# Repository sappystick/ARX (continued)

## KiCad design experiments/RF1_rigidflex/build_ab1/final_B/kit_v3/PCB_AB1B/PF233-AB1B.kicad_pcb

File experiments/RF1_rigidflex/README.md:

# RF1: rigid-flex redesign, side experiment (started 2026-10-29)

**Status: MODELED side experiment, phase 1 done.** Not part of the sign-off, the pipeline, the regress suite or any release. The baseline design is read and never written: every input the study reads is recorded with its sha256 in `results/rf1_phase1.json` together with the baseline commit. Any generator that a later phase changes is first copied into `experiments/RF1_rigidflex/src/` and changed there.

**Fixed (owner, 2026-10-29):** receive coils SB1R-QA/QB, the HTA antenna, the six TX formers and their litz, every printed part. **Free:** how the electronics are split into boards and how they connect: flex, rigid-flex or the circular rigid boards.

## Concepts

| | A: catalog FFC (B12 decision) | B: soldered flex jumpers | C: head rigid-flex (RF1 main line) |
|---|---|---|---|
| What | separate rigid boards, 0.5 mm FFC + connectors at the duct edges | separate rigid boards, custom 2-layer flex strips soldered / hot-bar bonded to pads (no connector) | AB1A + AB1B + CB1D + LB1 one rigid-flex panel (6L rigid sections, 2L flex core), HTA a flex tail, SB1R leads a soldered flex jumper |
| Hand joints in the head (today 66) | 18 (LB1, HTA and SB1R wires stay; the link becomes 4 reflowed connectors) | 12 bonded ends | 5 |
| Boards testable alone | yes | yes | no (panel test + test pads) |
| Fab | standard | standard + simple flex | rigid-flex vendor, every change re-spins the panel |

## Phase 1 results (`rf1_study.py`, MODELED / mesh-checked)

| Question | Result |
|---|---|
| AB1 <-> CB1D link fit on the meshes (link_path_check, imported unchanged) | baseline IDC ribbon 6 / 16 FAIL; catalog FFC 0 / 14; rigid-flex hinge (0.2 mm, no connector) 0 / 14 |
| Headroom (rigid-flex hinge) | 10.4 mm under LB1 (ribbon -4.4, FFC 8.4), 7.2 mm under the septum (ribbon -2.6, FFC 5.2) |
| CB1D -> LB1 hinge, CB1D -> HTA tail | rise 10.6 / 15.9 mm, S-fold needs 8.0 mm at a 2.0 mm fold radius (10 x 0.2 mm): both fit; flex about 15 / 21 mm |
| Receive-coil lead pair, 60 mm | loop area 10.2 mm2 (AWG36 touching) to 60 mm2 (loose 1 mm) today, 3.0 mm2 fixed on a broadside flex pair; capacitance about 5 pF either way |
| Eddy rule 5 | the board graph is a tree (no closed loop around the axis); hatched planes in the hinges; FR4 / polyimide stiffeners only (the vendor also offers stainless and aluminium: excluded) |
| Vendor (Rigiflex pages, `ds/`) | D228 fits the 18 x 24 in panel; 0.10 / 0.10 mm trace / space covers our finest; 6L 1.6 mm rigid-flex with 1 oz is a listed build; polyimide er 4, DF 0.04, water absorption 2.9 % |

What this does **not** show yet: any change in leak, noise or detection. The loop-area ratio is geometry only; the pickup needs the TX field along the lead path (phase 2).

## Where the real improvement is

1. **Build quality and repeatability (large, near certain):** 66 -> 5 hand joints in the head; the receive-lead loop area becomes a fixed 3 mm2 instead of 10-60 mm2 that depends on dressing, so the air leak becomes a calibratable constant instead of a per-unit variable. This is the gain RF1 can deliver for sure.
2. **Receive chain clean-sheet (large, MODELED next):** the AB1 sections are laid out from scratch in RF1, so the known receive defects go in at the same time: VREF / VCM buffer stability (OPEN_ITEMS 30), OPA2211 input range (31), chip-orientation robustness (B11), header pad rings (33). These are performance items; the flex is what lets the layout start over without the header constraint.
3. **Digital noise next to the receive coils (medium, to be modeled):** the ADC SPI (SCLK >= 27.2 MHz) runs between hatched ground layers in the hinge instead of an open ribbon.
4. **Not changed by RF1:** TX (litz, 20 A, 460 V taps stay wire, rules 5 / 6), the shaft cords (a 356 mm telescoping stroke needs dynamic flex: not proposed), the neck and handle boards.

## Phases

1. **Done:** census, mesh fit, fold radii, lead loop area, loop check, vendor fit (`results/rf1_phase1.json`, `results/rf1_head_concept.png`).
2. Receive-lead pickup: copy `sbq_sim.py` into `src/`, add the flex-tail path and the TX field along it; leak and its spread (wire dress Monte Carlo vs fixed flex). Hinge crosstalk SCLK -> RX input.
3. Clean-sheet AB1 section: copy `afe_design.py` / `afe_layout.py` into `src/`, apply items 30 / 31 (isolation resistor or reference driver; VCM / amplifier choice) and the rotating decoupling group (B11); route with the repo router.
4. Rigid-flex board definition: one outline with rigid and flex regions, stackup drawing (6L rigid, 2L flex core, coverlay, FR4 stiffeners), hinge routing with hatched GND, fold-line keep-outs (no vias or pads within 1 mm of a fold); DRC with drc.py per region; KiCad 9 has no per-region stackup, so the fab drawing carries it.
5. Compare A / B / C on the same table (fit, leak, noise, joints, test, cost from real quotes) and decide; only then does anything move into the main design (B12).

## Phase 2 results (`rf1_phase2.py`, on a copy of the receive simulation; MODELED)

Receive-lead pickup, 300 units per case, peak mV at turn-off (the same scale as the board leak in `kit_v22/sbq_sim.json`; lead path ASSUMED):

| QA board | mean | sigma | 95 % of units below |
|---|---|---|---|
| AWG36 untwisted (dress varies) | -1.6 | 26.8 | 49.3 |
| AWG36 twisted (5-15 mm pitch) | -0.03 | 0.69 | 1.27 |
| flex broadside pair at the design orientation | 0.09 | 0.15 | 0.31 |
| flex at the worst orientation (routed carelessly) | 3.0 | - | - |
| board leak for comparison: aligned / 0.1 mm / 0.5 mm offset | 0.008 / 0.015 / 0.13 | | |

The lead pair is part of the receive null: untwisted wire alone is 100-1000 x the aligned board leak. Flex cuts the unit-to-unit spread 4-5 x against a good twisted pair, and its mean is a fixed offset (calibratable). The flex must be routed at the design orientation (loop plane along the field): rule for phase 4. QB: 15.6 / 0.63 / 0.08 mV sigma.

Clock crosstalk into the analog lines of the AB1 <-> CB1D link (2D finite-difference C and L, upper bounds on a 100 pF node, 3.3 V edge in 2 ns):

| victim | ribbon (today) | RF1 hinge (guard traces + ground layer) |
|---|---|---|
| MONO_IN, worst aggressor | 437 mV | 7.1 mV |
| MONO_IN from SCLK | 62 mV | 0.22 mV |
| VCM_OUT, worst aggressor | 215 mV | 1.4 mV |

## Cavity and potting (`rf1_cavity.py`, MODELED, envelope volumes)

With hinges instead of headers and three part swaps on CB1D (OKI-78SR module -> TI LMR36015 + Bourns SRN4018-6R8M; Pico 2 W on pins -> chip-down RP2354A without the radio; headers -> hinges), the tallest CB1D part is 2.5 mm (was 10.2) and the tallest AB1 part 1.6 mm (was the 4 mm header + 5 mm socket).

| layer | baseline | needs | saving |
|---|---|---|---|
| L1 gallery | 5.8 | 2.2 | 3.6 |
| L2 analog cell | 10.2 | 6.05 | 4.15 |
| L5 controller | 11.8 | 5.1 | 6.7 |

- **K-top (recommended):** L0-L4 keep their z (nothing near the receive coils moves); L5 shrinks 6.7 mm: head 47.1 -> 40.4 mm. L5 becomes a potted zone (syntactic silicone, 22.8 cm3, 13.7-18.3 g) instead of coat-only: the tube saves 13.7 g, so the head mass is about unchanged (0 to +4.6 g); the gain is protection (moisture, microphonics, better heat path than still air). To re-run: head_crosscheck, the HTA coupling (it moves 6.7 mm toward the formers), head thermal with the pour.
- **S (full shrink):** 14.5 mm (head 32.6 mm), but AB1, the septum and the carbonyl-iron absorber move 3.6-7.8 mm toward the receive coils: changes the receive null; not before sbq_sim / check_v22 / head_crosscheck say so.
- Potting: L1 gallery and L2 gel (fixed flex, no connector voids), L4 CI unchanged, L5 SYN (new), every hinge bend outside the pours, LB1 / HTA coat only.

## Phase 4: the head rigid-flex definition (`rf1_phase4.py`, MODELED)

- **Stackup:** 6-layer rigid sections (F, In1 hatched GND, In2, In3, In4 plane / +3V3D island, B) with the 2-layer flex core as In2 / In3: hinge signals leave on In2 over a hatched In3 ground. Rigid 1.602 mm, flex 0.186 mm (vendor: 1.6 / 0.2). LB1 goes 4 -> 6 layers; HTA stays a separate 4-layer board with a hot-bar flex tail (the roof stays removable).
- **Flattened panel:** CB1D at the centre, LB1 across its 15.2 mm S-fold, AB1A / AB1B at the ends of L-shaped 7 mm hinges that leave the CB1D duct edge either side of the LB1 hinge: 332 x 171 mm, fits the 457 x 610 mm panel; copper is 24.5 % of the box (expect a high panel price: get quotes).
- **Fold and transition rules F1-F8:** no via / pad within 1.0 mm of a transition; traces cross folds at 90 deg, no corners or width changes in a bend zone; cross-hatched flex ground; fold radius >= 2.0 mm, static only; FR4 / polyimide stiffeners only (rule 5); no 460 V net on any flex (rule 6); no rigid pour across a fold; ground guards on both sides of every analog hinge line. ASSUMED until the vendor and IPC-2223 confirm.
- **CB1D section:** Pico 2 W module and OKI-78SR leave; RP2354A (QFN-60) + 12 MHz crystal + core inductor + TLV755P 3.3 V and LMR36015 + SRN4018-6R8M come in, placed in the freed areas with 0.3 mm to every kept part (`results/rf1_cb1d_section.png`). The radio leaves with the Pico W (OPEN_ITEMS 42 settled by removal). CB1D is not re-routed in RF1 yet.

## Phase 3: clean-sheet AB1 (`src/ab1/`, MODELED)

`make_rf1_ab1.py` builds the RF1 generator as checked patches of the baseline `afe_design.py` / `afe_layout.py` / `afe_ripup.py`. Changes: hinge-exit lands (J2) and flex-jumper lands (J1) instead of headers; OPA2211 reference VBIAS = 2.5 V (REFOUT through OPA2365 half A, 10 ohm isolation, 1 uF); 1:2 divider into each ADC input (AIN+ 1.25 V DC = VCM); RF 820 ohm (total gain 41.5); 10 ohm isolation on the VCM buffer (OPEN_ITEMS 30); local TLV755P +3V3D next to the ADC island (the hinge no longer carries +3V3D; pin 3 is a ground).

Front-end check (`rf1_frontend_check.py`, against TI SBOS377L and the AD7389-4 Rev. 0): baseline **FAIL** (OPA2211 input 1.25 V, range 2.0-3.6 V); RF1 **PASS** (input 2.5 V, ADC common mode 1.25 V inside 0.2-2.3, offset 0 by construction, 38 % of the ADC differential range used vs 42 % baseline, divider noise 0.1 nV/rtHz vs 1.1 for the amplifier, closed-loop bandwidth 0.96 MHz vs the 318 kHz filter).

Routing (the repo's AB1 router, unchanged rules: track 0.15, clearance 0.16, via 0.508 / 0.254):

- **Routing status: AB1B routed: 0 open; KiCad 9 DRC 0 errors / 0 unconnected (20 dangling-track warnings, the baseline has 19); independent DRC 0 fails, minimum clearance 0.204 mm** (`build_ab1/final_B/`, `results/rf1_ab1_route.json`).
- AB1A: best 2 open (the reference buffer's input and its isolation resistor), see the repair-loop record in `results/rf1_ab1_route.json` when it closes.
- How: the hinge exit (J2 lands) sits where the baseline header was (east edge, next to the ADC) and the hinge folds up there; the north exit toward the duct left 3-15 nets open. Placement of the RF1 parts (and, on AB1B, D2 / RF1 / CF1 nudged in a 2 mm window) is automatic: `src/ab1/autoplace_rf1.py` (pads and bodies checked, 0.5 mm corridor margin, caps anchored to their pins) and `src/ab1/repair_loop.py` (re-places only the parts within 2.5-5.5 mm of a stuck pin, keeps a result only if fewer nets are open).
- Tried and dropped (recorded in the generator as options, off): matched AIN- dividers (more parts, 8-15 open), swapped buffer halves (the LDO then blocks the +3V3D island), no local LDO on AB1A (5-8 open), the north hinge exit (3-15 open).

## Baseline defect found here (recorded in docs/CORRECTIONS.md, 2026-10-29)

The committed AD7389-4 AB1 biases the OPA2211 inputs at VCM = 1.25 V, below their 2.0 V minimum on a single 5 V supply (TI SBOS377L). RF1 fixes it (phase 3).

## Files

- `rf1_study.py` phase 1 study; `rf1_figure.py` the figure; `rf1_phase2.py` lead pickup and crosstalk; `rf1_cavity.py` condensation and potting;
  `src/ab1/make_rf1_ab1.py` the clean-sheet AB1 as checked patches of the baseline generator (writes the RF1 copies `afe_design.py`, `afe_layout.py`, `afe_ripup.py`);
  `rf1_phase4.py` stackup, flattened panel, fold rules, CB1D section; `results/` outputs; `ds/` the Rigiflex pages (owner-supplied, 2026-10-29); `src/sbq_sim_baseline_copy.py` the receive simulation copy.

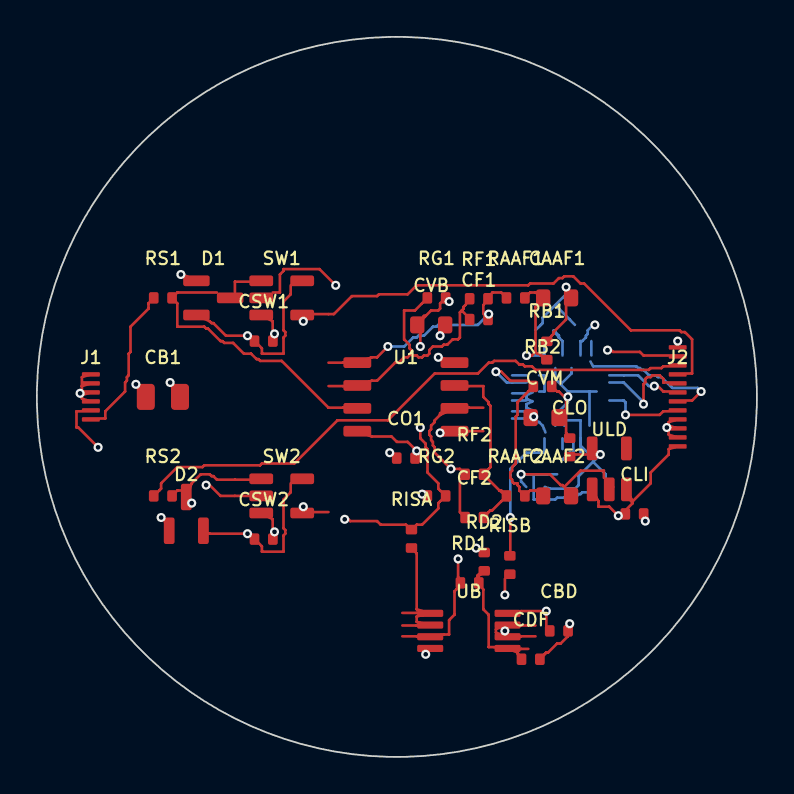
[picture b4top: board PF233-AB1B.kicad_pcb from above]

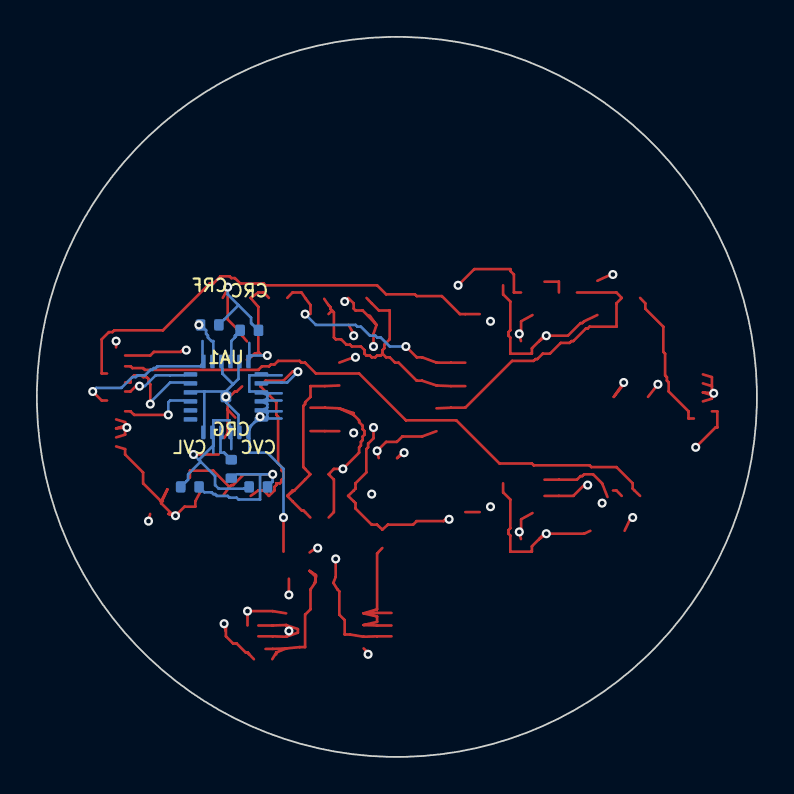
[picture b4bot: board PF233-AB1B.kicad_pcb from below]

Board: 6 copper layers, 40.0 x 40.0 mm, 43 parts (6 on the bottom side), 26 nets.

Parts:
CAAF1, CAAF2: 1n; C_0603_1608Metric
CB1: 10u; C_0805_2012Metric
CBD: 100n; C_0402_1005Metric
CDF: 100n; C_0402_1005Metric
CF1, CF2: 22p; C_0402_1005Metric
CLI: 1u; C_0402_1005Metric
CLO: 1u; C_0402_1005Metric
CO1: 100n; C_0402_1005Metric
CRC: 100n; C_0402_1005Metric
CRF: 1u; C_0402_1005Metric
CRG: 1u; C_0402_1005Metric
CSW1, CSW2: 100n; C_0402_1005Metric
CVB: 1u; C_0603_1608Metric
CVC: 1u; C_0402_1005Metric
CVL: 1u; C_0402_1005Metric
CVM: 1u; C_0603_1608Metric
D1, D2: BAV199; SOT-23
J1: RF1 receive-coil flex jumper lands 6p; FPC_6_P0.5
J2: RF1 rigid-flex hinge exit 12p; FPC_12_P0.5
RAAF1, RAAF2: 1k; R_0402_1005Metric
RB1, RB2: 1k; R_0402_1005Metric
RD1, RD2: 100k; R_0402_1005Metric
RF1, RF2: 820; R_0402_1005Metric
RG1, RG2: 10; R_0402_1005Metric
RISA: 10; R_0402_1005Metric
RISB: 10; R_0402_1005Metric
RS1, RS2: 1000; R_0402_1005Metric
SW1, SW2: 74LVC1G66; SOT-23-5
U1: OPA2211; SOIC-8_3.9x4.9mm_P1.27mm
UA1: AD7389-4; CP-24-25_ADI_LFCSP-24-1EP_4x4mm_P0.5mm_EP0.61x0.61mm
UB: OPA2365; MSOP-8_3x3mm_P0.65mm
ULD: TLV755P33; SOT-23-5

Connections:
+3V3D: CLO.1, CVC.1, CVL.1, UA1.2, UA1.4, ULD.5
+5VA: CB1.1, CBD.1, CLI.1, CO1.1, CSW1.1, CSW2.1, D1.2, D2.2, J2.1, SW1.5, SW2.5, U1.8, UB.8, ULD.1, ULD.3
ADCIN_MONO: CAAF2.1, RAAF2.2, RB2.1, UA1.11
ADCIN_Y8: CAAF1.1, RAAF1.2, RB1.1, UA1.13
BLANK: J2.9, SW1.4, SW2.4
CS: J2.6, UA1.18
FB_MONO: CF2.1, RF2.1, RG2.1, U1.6
FB_Y8: CF1.1, RF1.1, RG1.1, U1.2
GND: CAAF1.2, CAAF2.2, CB1.2, CBD.2, CDF.2, CLI.2, CLO.2, CO1.2, CRC.2, CRF.2, CRG.2, CSW1.2, CSW2.2, CVB.2, CVC.2, CVL.2, CVM.2, D1.1, D2.1, J1.3, J1.4, J1.5, J1.6, J2.2, J2.3, J2.4, J2.12, RB1.2, RB2.2, RD2.2, SW1.3, SW2.3, U1.4, UA1.1, UA1.5, UA1.14, UA1.16, UA1.21, UA1.25, UB.4, ULD.2
IN_MONO: D2.3, RS2.2, SW2.1, U1.5
IN_Y8: D1.3, RS1.2, SW1.1, U1.3
OUT_MONO: CF2.2, RAAF2.1, RF2.2, U1.7
OUT_Y8: CF1.2, RAAF1.1, RF1.2, U1.1
RAW_MONO: J2.10, RS2.1
RAW_Y8: J1.1, RS1.1
REFCAP: CRC.1, UA1.15
REGCAP: CRG.1, UA1.3
SCLK: J2.5, UA1.22
SDO1: J2.7, UA1.19
SDO2: J2.8, UA1.20
VBIAS: CVB.1, J1.2, J2.11, RG1.2, RG2.2, RISA.2, SW1.2, SW2.2
VBIAS_O: RISA.1, UB.1, UB.2
VCM: CVM.1, RISB.2, UA1.6, UA1.7, UA1.8, UA1.9, UA1.10, UA1.12
VCM_DIV: CDF.1, RD1.2, RD2.1, UB.5
VCM_O: RISB.1, UB.6, UB.7
VREF_RAW: CRF.1, RD1.1, UA1.17, UB.3

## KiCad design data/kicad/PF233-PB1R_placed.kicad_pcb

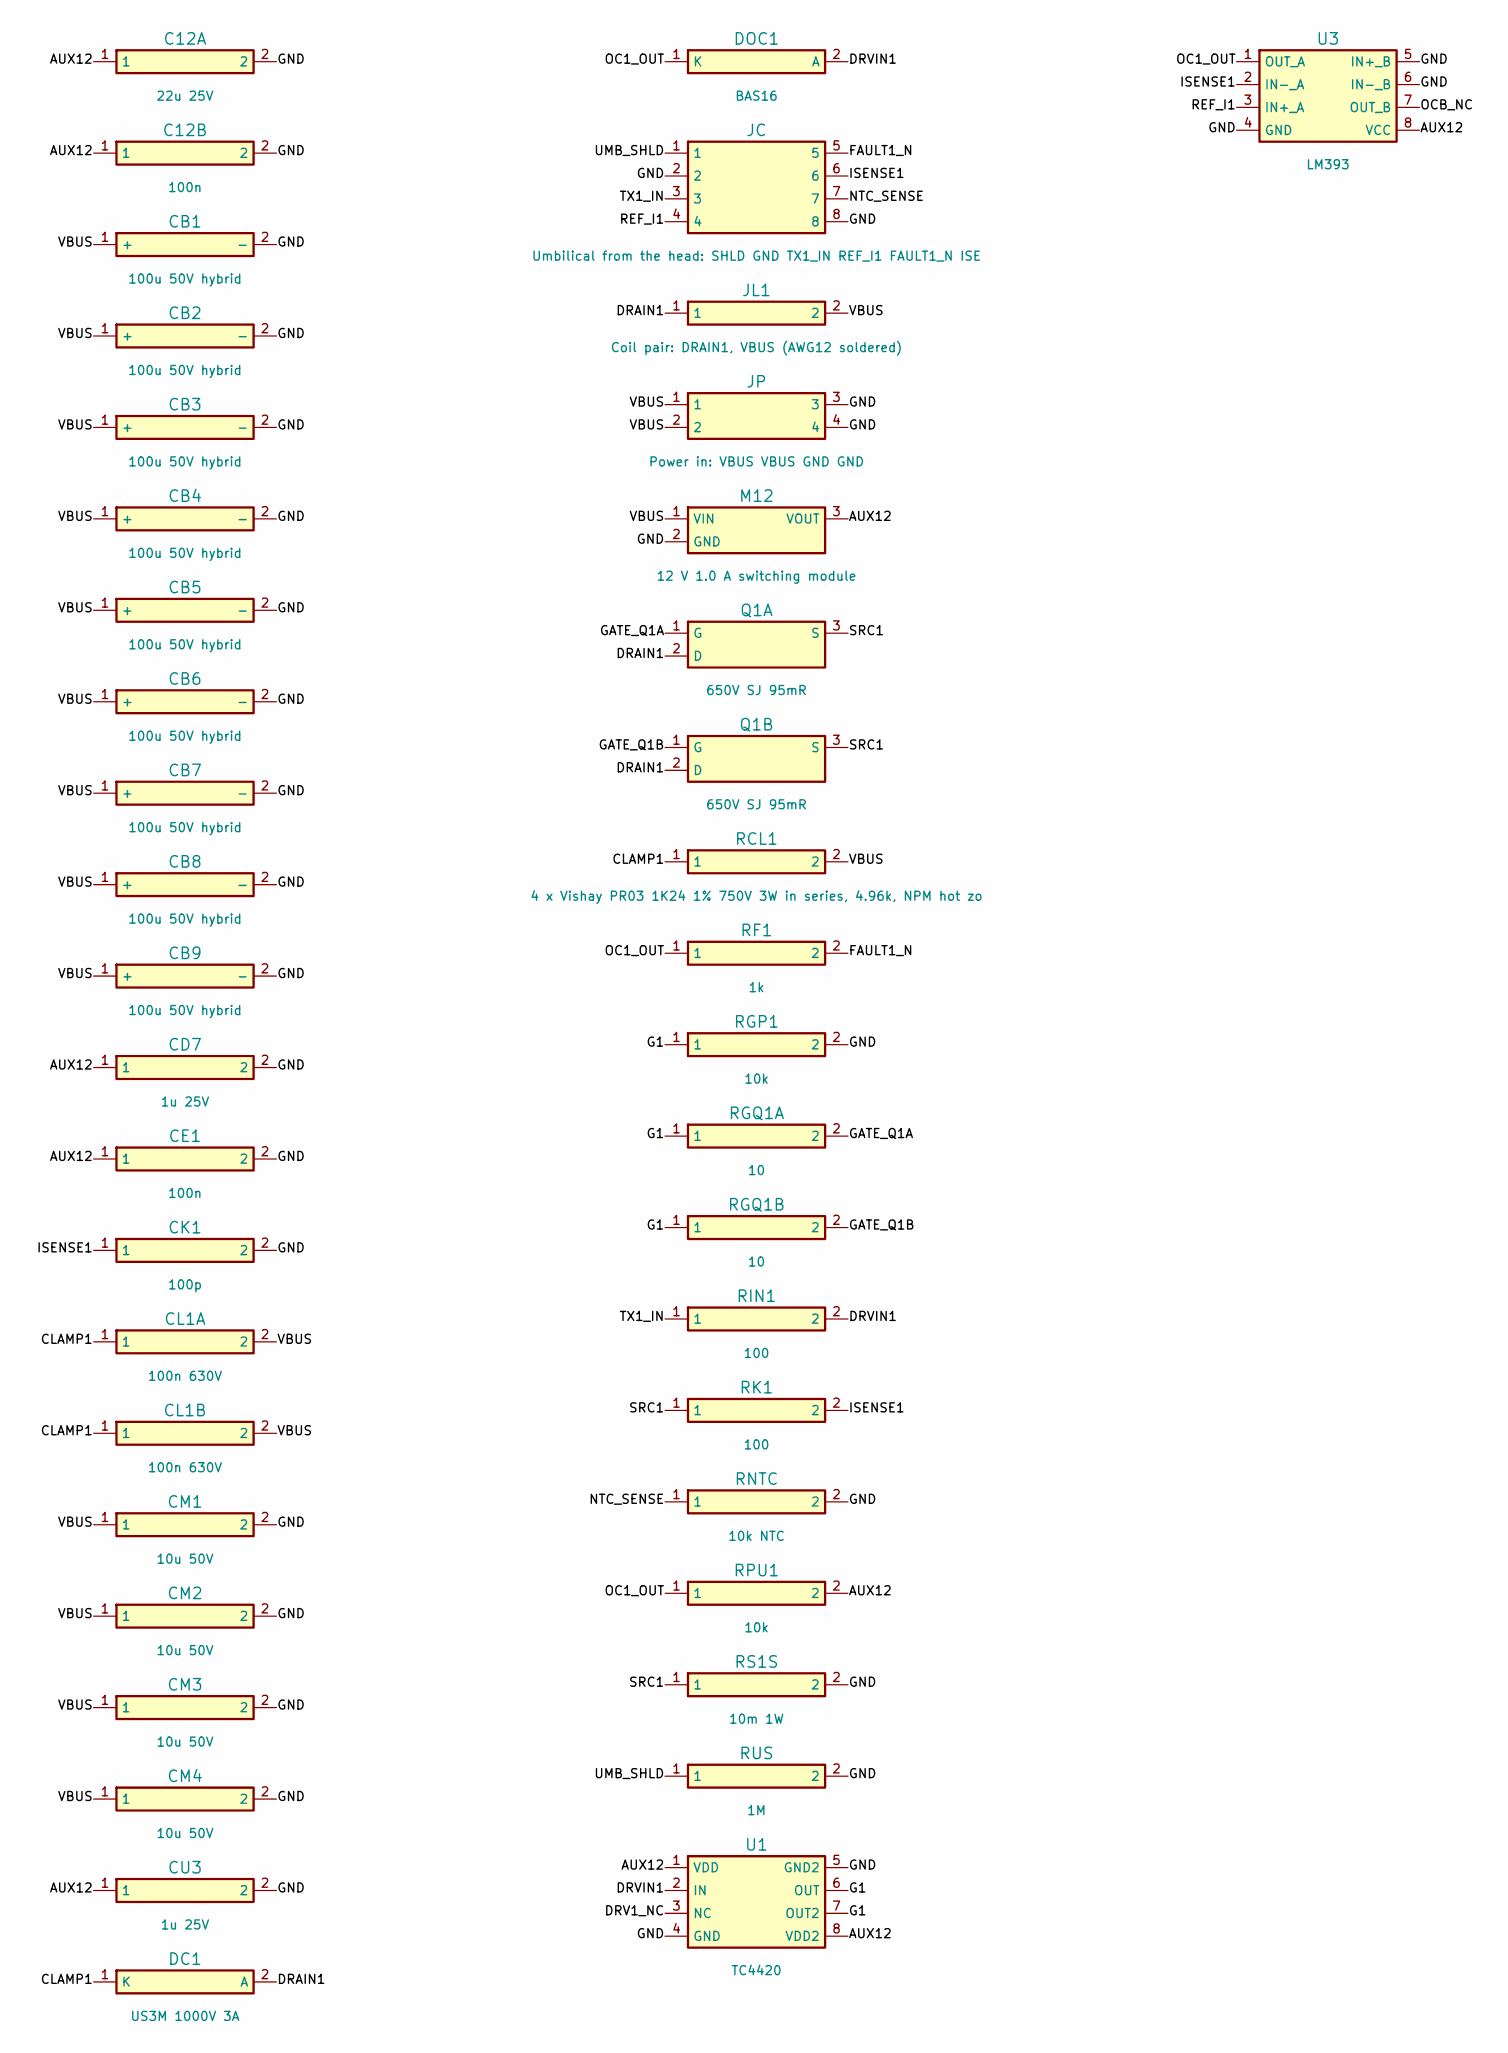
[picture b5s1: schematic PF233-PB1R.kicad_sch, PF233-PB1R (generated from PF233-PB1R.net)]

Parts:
C12A: 22u 25V; C_1210_3225Metric
C12B: 100n; C_0603_1608Metric
CB1, CB2, CB3, CB4, CB5, CB6, CB7, CB8, CB9: 100u 50V hybrid; CP_Elec_10x10
CD7: 1u 25V; C_0805_2012Metric
CE1: 100n; C_0603_1608Metric
CK1: 100p; C_0603_1608Metric
CL1A, CL1B: 100n 630V; C_1210_3225Metric
CM1, CM2, CM3, CM4: 10u 50V; C_1210_3225Metric
CU3: 1u 25V; C_0805_2012Metric
DC1: US3M 1000V 3A; D_SMC
DOC1: BAS16; D_SOD-123
JC: Umbilical from the head: SHLD GND TX1_IN REF_I1 F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; Wire_pads_2x4_P2.54mm
JL1: Coil pair: DRAIN1, VBUS (AWG12 soldered); Wire_pads_AWG12_1x2_P5.08mm
JP: Power in: VBUS VBUS GND GND; Wire_pads_1x4_P5.08mm
M12: 12 V 1.0 A switching module; Converter_DCDC_Murata_OKI-78SR_Horizontal
Q1A, Q1B: 650V SJ 95mR; TO-263-3_TabPin2
RCL1: 4 x Vishay PR03 1K24 1% 750V 3W in series, 4.96k,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; SolderPad_2x_P5.08mm
RF1: 1k; R_0603_1608Metric
RGP1: 10k; R_0603_1608Metric
RGQ1A, RGQ1B: 10; R_0603_1608Metric
RIN1: 100; R_0603_1608Metric
RK1: 100; R_0603_1608Metric
RNTC: 10k NTC; R_0603_1608Metric
RPU1: 10k; R_0603_1608Metric
RS1S: 10m 1W; R_2512_6332Metric
RUS: 1M; R_0603_1608Metric
U1: TC4420; SOIC-8_3.9x4.9mm_P1.27mm
U3: LM393; SOIC-8_3.9x4.9mm_P1.27mm

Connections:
AUX12: C12A.1, C12B.1, CD7.1, CE1.1, CU3.1, M12.3 (VOUT), RPU1.2, U1.1 (VDD), U1.8 (VDD2), U3.8 (VCC)
CLAMP1: CL1A.1, CL1B.1, DC1.1 (K), RCL1.1
DRAIN1: DC1.2 (A), JL1.1, Q1A.2 (D), Q1B.2 (D)
DRV1_NC: U1.3 (NC)
DRVIN1: DOC1.2 (A), RIN1.2, U1.2 (IN)
FAULT1_N: JC.5, RF1.2
G1: RGP1.1, RGQ1A.1, RGQ1B.1, U1.6 (OUT), U1.7 (OUT2)
GATE_Q1A: Q1A.1 (G), RGQ1A.2
GATE_Q1B: Q1B.1 (G), RGQ1B.2
GND: C12A.2, C12B.2, CB1.2 (-), CB2.2 (-), CB3.2 (-), CB4.2 (-), CB5.2 (-), CB6.2 (-), CB7.2 (-), CB8.2 (-), CB9.2 (-), CD7.2, CE1.2, CK1.2, CM1.2, CM2.2, CM3.2, CM4.2, CU3.2, JC.2, JC.8, JP.3, JP.4, M12.2 (GND), RGP1.2, RNTC.2, RS1S.2, RUS.2, U1.4 (GND), U1.5 (GND2), U3.4 (GND), U3.5 (IN+_B), U3.6 (IN-_B)
ISENSE1: CK1.1, JC.6, RK1.2, U3.2 (IN-_A)
NTC_SENSE: JC.7, RNTC.1
OC1_OUT: DOC1.1 (K), RF1.1, RPU1.1, U3.1 (OUT_A)
OCB_NC: U3.7 (OUT_B)
REF_I1: JC.4, U3.3 (IN+_A)
SRC1: Q1A.3 (S), Q1B.3 (S), RK1.1, RS1S.1
TX1_IN: JC.3, RIN1.1
UMB_SHLD: JC.1, RUS.1
VBUS: CB1.1 (+), CB2.1 (+), CB3.1 (+), CB4.1 (+), CB5.1 (+), CB6.1 (+), CB7.1 (+), CB8.1 (+), CB9.1 (+), CL1A.2, CL1B.2, CM1.1, CM2.1, CM3.1, CM4.1, JL1.2, JP.1, JP.2, M12.1 (VIN), RCL1.2

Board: 4 copper layers, 42 parts (0 on the bottom side), 17 nets, no tracks yet.

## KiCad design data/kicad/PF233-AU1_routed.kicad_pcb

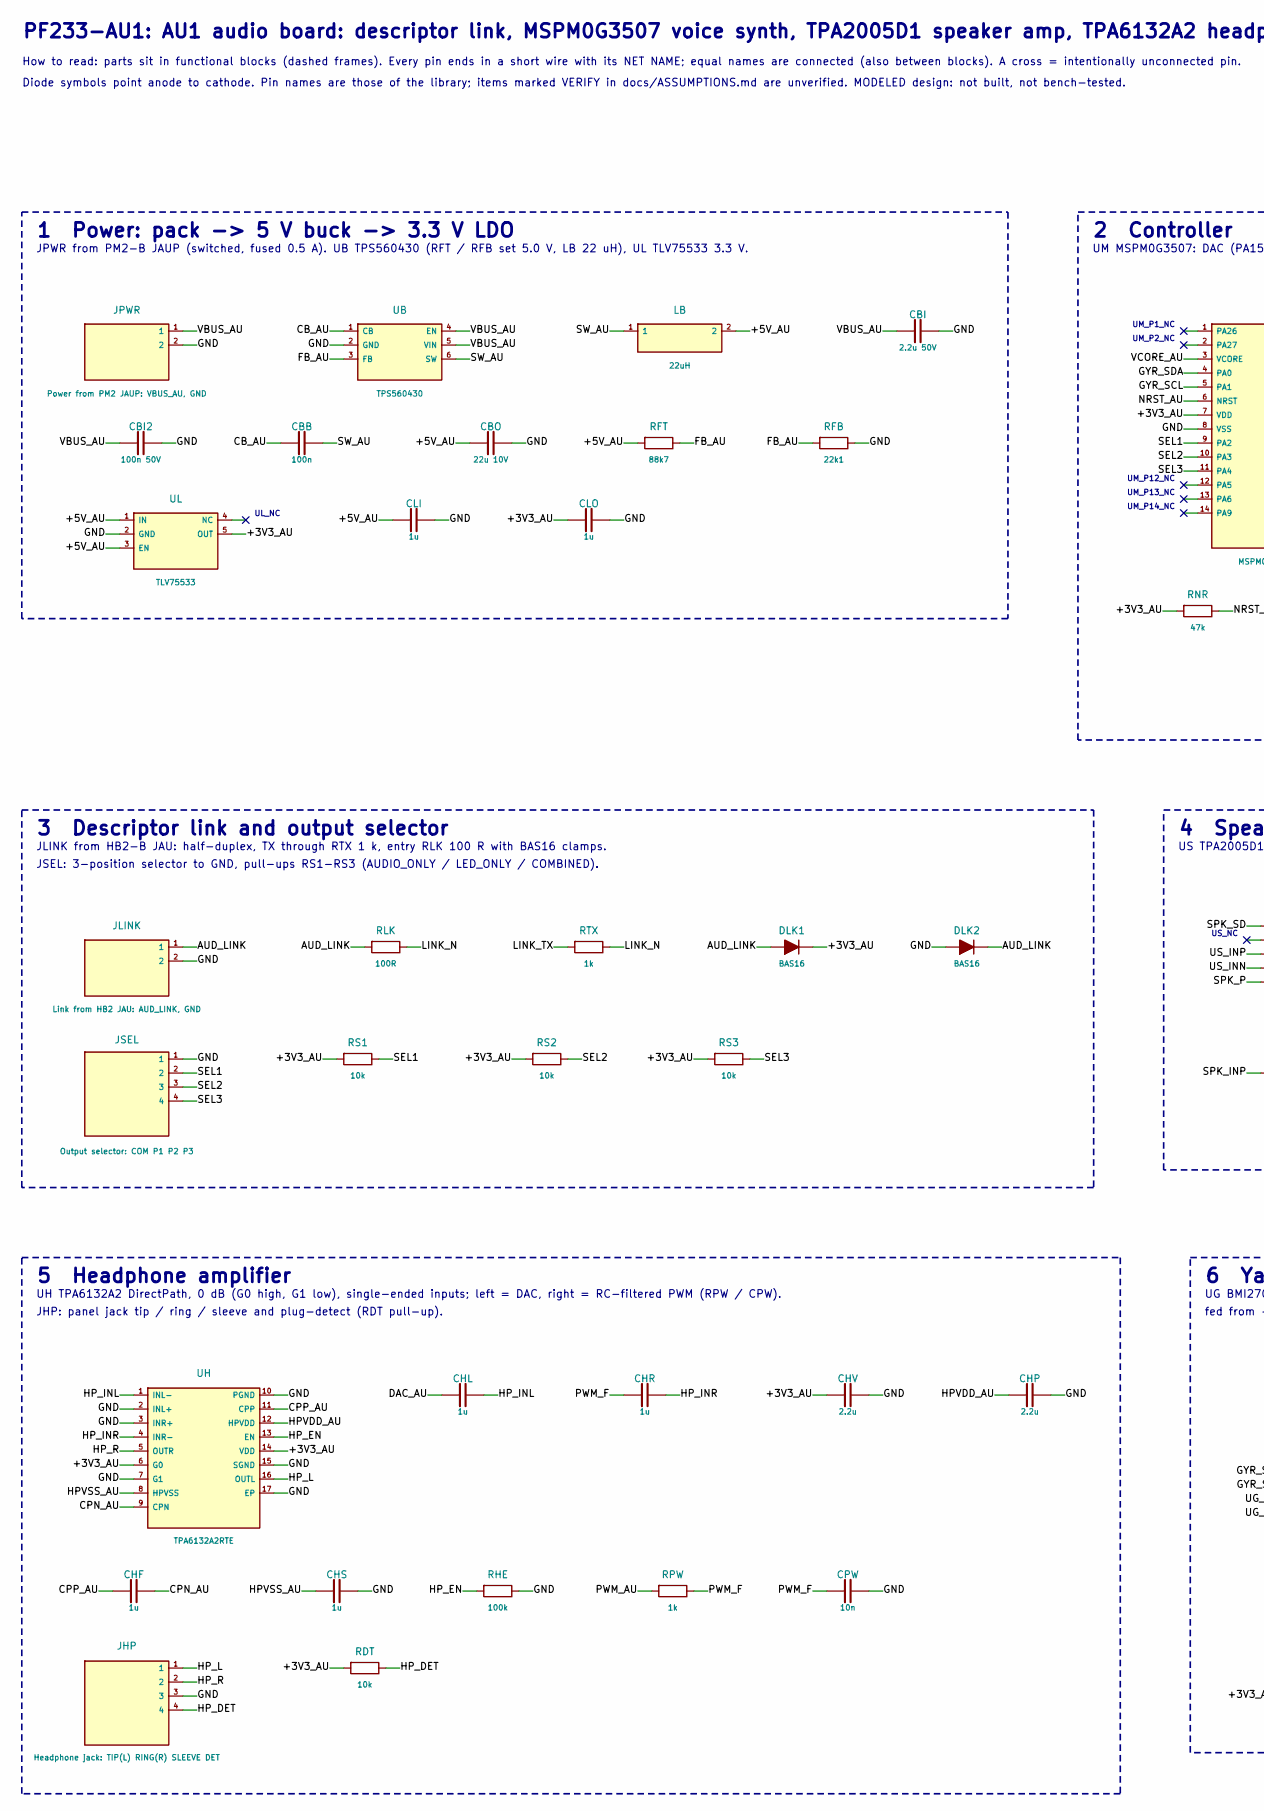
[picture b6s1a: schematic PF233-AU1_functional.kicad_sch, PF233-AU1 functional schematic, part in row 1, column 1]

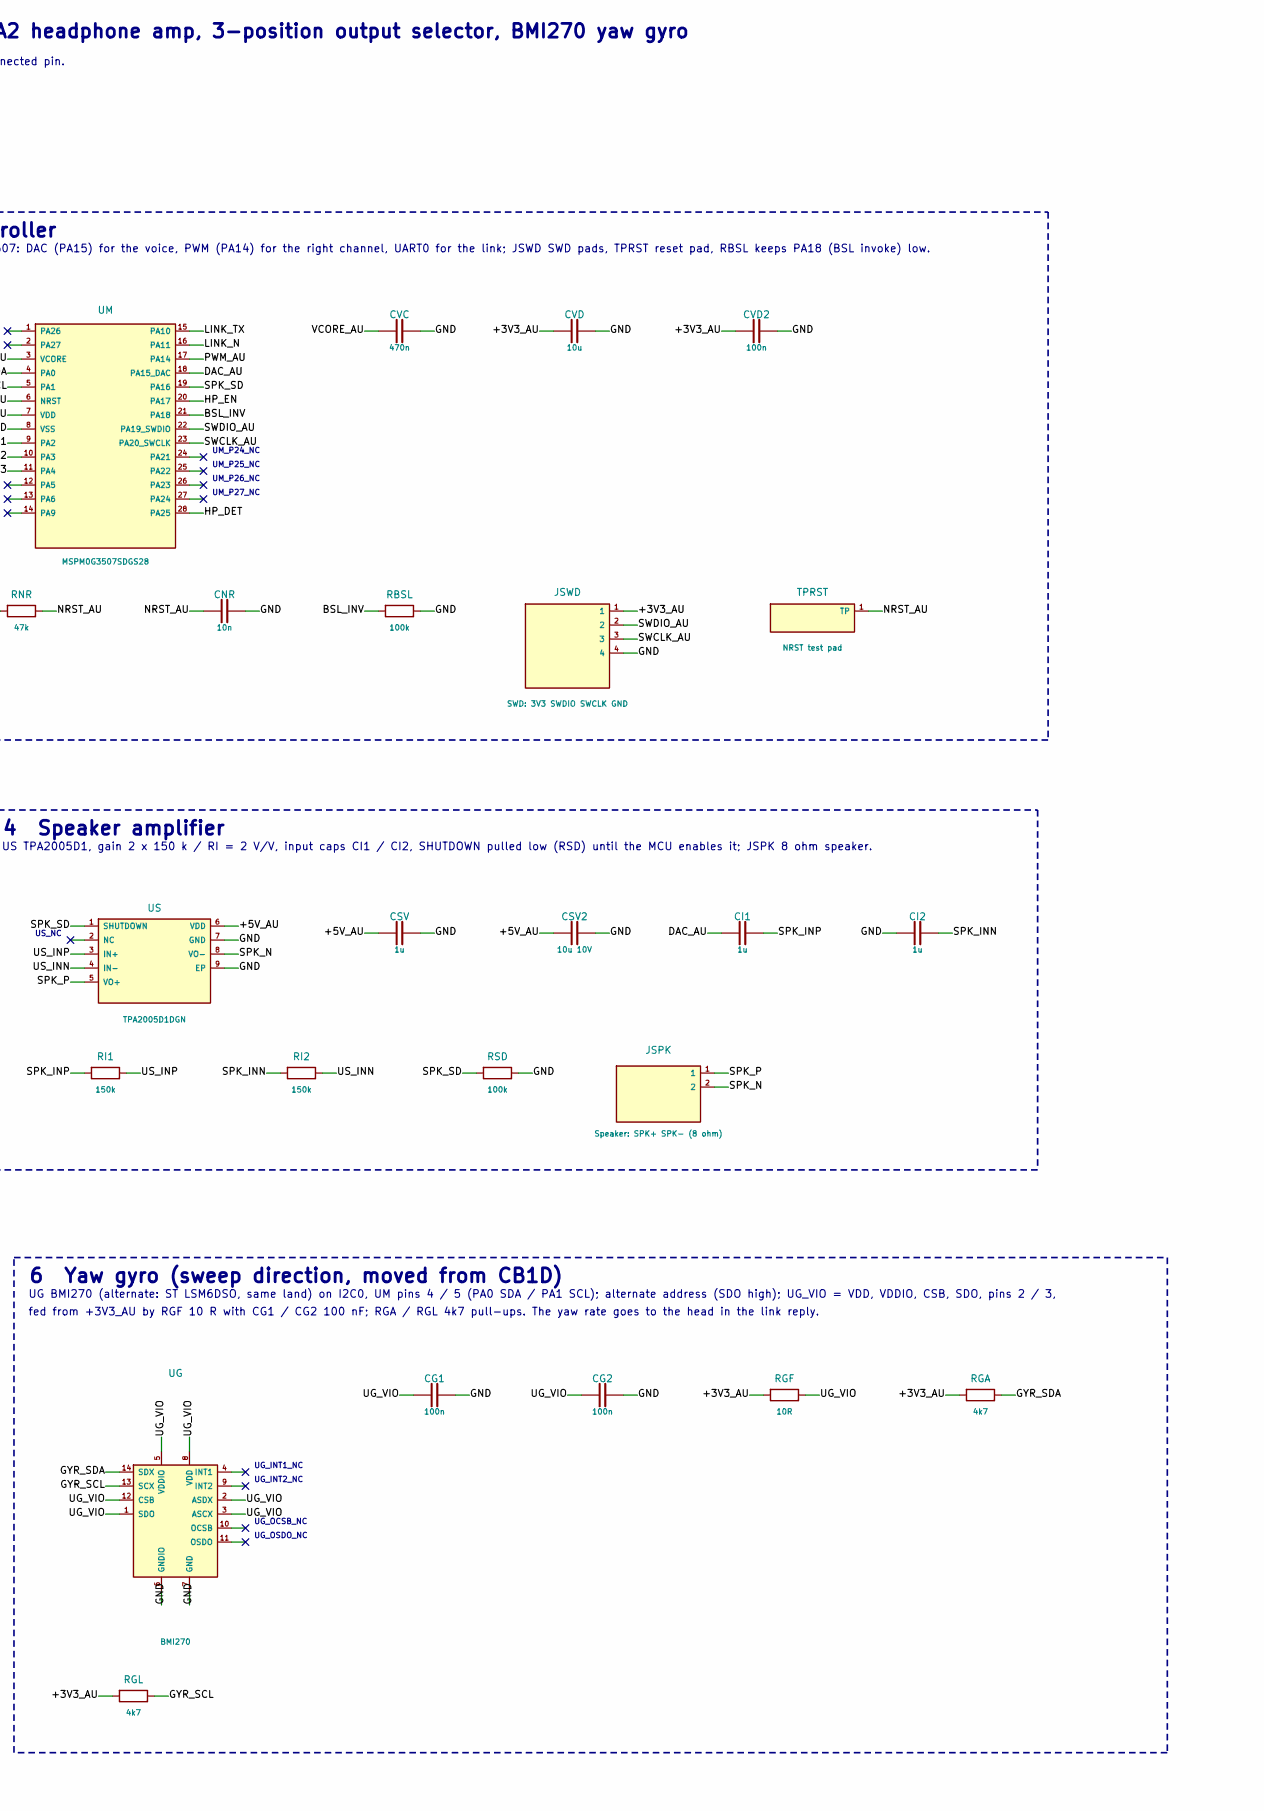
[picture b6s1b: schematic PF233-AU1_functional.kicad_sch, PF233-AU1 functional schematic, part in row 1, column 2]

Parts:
CBB: 100n; C_0603_1608Metric
CBI: 2.2u 50V; C_1210_3225Metric
CBI2: 100n 50V; C_0603_1608Metric
CBO: 22u 10V; C_1210_3225Metric
CG1, CG2: 100n; C_0603_1608Metric
CHF: 1u; C_0603_1608Metric
CHL: 1u; C_0603_1608Metric
CHP: 2.2u; C_0603_1608Metric
CHR: 1u; C_0603_1608Metric
CHS: 1u; C_0603_1608Metric
CHV: 2.2u; C_0603_1608Metric
CI1, CI2: 1u; C_0603_1608Metric
CLI: 1u; C_0603_1608Metric
CLO: 1u; C_0603_1608Metric
CNR: 10n; C_0603_1608Metric
CPW: 10n; C_0603_1608Metric
CSV: 1u; C_0603_1608Metric
CSV2: 10u 10V; C_1210_3225Metric
CVC: 470n; C_0603_1608Metric
CVD: 10u; C_0805_2012Metric
CVD2: 100n; C_0603_1608Metric
DLK1, DLK2: BAS16; D_SOD-123
JHP: Headphone jack: TIP(L) RING(R) SLEEVE DET; Wire_pads_1x4_P5.08mm
JLINK: Link from HB2 JAU: AUD_LINK, GND; SolderPad_2x_P5.08mm
JPWR: Power from PM2 JAUP: VBUS_AU, GND; SolderPad_2x_P5.08mm
JSEL: Output selector: COM P1 P2 P3; Wire_pads_1x4_P5.08mm
JSPK: Speaker: SPK+ SPK- (8 ohm); SolderPad_2x_P5.08mm
JSWD: SWD: 3V3 SWDIO SWCLK GND; Wire_pads_1x4_P2.54mm
LB: 22uH; L_Bourns_SRN4018
RBSL: 100k; R_0603_1608Metric
RDT: 10k; R_0603_1608Metric
RFB: 22k1; R_0603_1608Metric
RFT: 88k7; R_0603_1608Metric
RGA: 4k7; R_0603_1608Metric
RGF: 10R; R_0603_1608Metric
RGL: 4k7; R_0603_1608Metric
RHE: 100k; R_0603_1608Metric
RI1, RI2: 150k; R_0603_1608Metric
RLK: 100R; R_0603_1608Metric
RNR: 47k; R_0603_1608Metric
RPW: 1k; R_0603_1608Metric
RS1, RS2, RS3: 10k; R_0603_1608Metric
RSD: 100k; R_0603_1608Metric
RTX: 1k; R_0603_1608Metric
TPRST: NRST test pad; TestPad_1.5mm
UB: TPS560430; SOT-23-6
UG: BMI270; BMI270_LGA-14_2.5x3.0mm
UH: TPA6132A2RTE; WQFN-16-1EP_3x3mm_P0.5mm
UL: TLV75533; SOT-23-5
UM: MSPM0G3507SDGS28; VSSOP-28_4.4x7.1mm_P0.5mm
US: TPA2005D1DGN; HVSSOP-8-1EP_3x3mm_P0.65mm

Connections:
+3V3_AU: CHV.1, CLO.1, CVD.1, CVD2.1, DLK1.1, JSWD.1, RDT.1, RGA.1, RGF.1, RGL.1, RNR.1, RS1.1, RS2.1, RS3.1, UH.6 (G0), UH.14 (VDD), UL.5 (OUT), UM.7 (VDD)
+5V_AU: CBO.1, CLI.1, CSV.1, CSV2.1, LB.2, RFT.1, UL.1 (IN), UL.3 (EN), US.6 (VDD)
AUD_LINK: DLK1.2, DLK2.1, JLINK.1, RLK.1
BSL_INV: RBSL.1, UM.21 (PA18)
CB_AU: CBB.1, UB.1 (CB)
CPN_AU: CHF.2, UH.9 (CPN)
CPP_AU: CHF.1, UH.11 (CPP)
DAC_AU: CHL.1, CI1.1, UM.18 (PA15_DAC)
FB_AU: RFB.1, RFT.2, UB.3 (FB)
GND: CBI.2, CBI2.2, CBO.2, CG1.2, CG2.2, CHP.2, CHS.2, CHV.2, CI2.1, CLI.2, CLO.2, CNR.2, CPW.2, CSV.2, CSV2.2, CVC.2, CVD.2, CVD2.2, DLK2.2, JHP.3, JLINK.2, JPWR.2, JSEL.1, JSWD.4, RBSL.2, RFB.2, RHE.2, RSD.2, UB.2 (GND), UG.6 (GNDIO), UG.7 (GND), UH.2 (INL+), UH.3 (INR+), UH.7 (G1), UH.10 (PGND), UH.15 (SGND), UH.17 (EP), UL.2 (GND), UM.8 (VSS), US.7 (GND), US.9 (EP)
GYR_SCL: RGL.2, UG.13 (SCX), UM.5 (PA1)
GYR_SDA: RGA.2, UG.14 (SDX), UM.4 (PA0)
HPVDD_AU: CHP.1, UH.12 (HPVDD)
HPVSS_AU: CHS.1, UH.8 (HPVSS)
HP_DET: JHP.4, RDT.2, UM.28 (PA25)
HP_EN: RHE.1, UH.13 (EN), UM.20 (PA17)
HP_INL: CHL.2, UH.1 (INL-)
HP_INR: CHR.2, UH.4 (INR-)
HP_L: JHP.1, UH.16 (OUTL)
HP_R: JHP.2, UH.5 (OUTR)
LINK_N: RLK.2, RTX.2, UM.16 (PA11)
LINK_TX: RTX.1, UM.15 (PA10)
NRST_AU: CNR.1, RNR.2, TPRST.1, UM.6 (NRST)
PWM_AU: RPW.1, UM.17 (PA14)
PWM_F: CHR.1, CPW.1, RPW.2
SEL1: JSEL.2, RS1.2, UM.9 (PA2)
SEL2: JSEL.3, RS2.2, UM.10 (PA3)
SEL3: JSEL.4, RS3.2, UM.11 (PA4)
SPK_INN: CI2.2, RI2.1
SPK_INP: CI1.2, RI1.1
SPK_N: JSPK.2, US.8 (VO-)
SPK_P: JSPK.1, US.5 (VO+)
SPK_SD: RSD.1, UM.19 (PA16), US.1 (SHUTDOWN)
SWCLK_AU: JSWD.3, UM.23 (PA20_SWCLK)
SWDIO_AU: JSWD.2, UM.22 (PA19_SWDIO)
SW_AU: CBB.2, LB.1, UB.6 (SW)
UG_INT1_NC: UG.4 (INT1)
UG_INT2_NC: UG.9 (INT2)
UG_OCSB_NC: UG.10 (OCSB)
UG_OSDO_NC: UG.11 (OSDO)
UG_VIO: CG1.1, CG2.1, RGF.2, UG.1 (SDO), UG.2 (ASDX), UG.3 (ASCX), UG.5 (VDDIO), UG.8 (VDD), UG.12 (CSB)
UL_NC: UL.4 (NC)
UM_P1_NC: UM.1 (PA26)
UM_P2_NC: UM.2 (PA27)
UM_P12_NC: UM.12 (PA5)
UM_P13_NC: UM.13 (PA6)
UM_P14_NC: UM.14 (PA9)
UM_P24_NC: UM.24 (PA21)
UM_P25_NC: UM.25 (PA22)
UM_P26_NC: UM.26 (PA23)
UM_P27_NC: UM.27 (PA24)
US_INN: RI2.2, US.4 (IN-)
US_INP: RI1.2, US.3 (IN+)
US_NC: US.2 (NC)
VBUS_AU: CBI.1, CBI2.1, JPWR.1, UB.4 (EN), UB.5 (VIN)
VCORE_AU: CVC.1, UM.3 (VCORE)

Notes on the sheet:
How to read: parts sit in functional blocks (dashed frames). Every pin ends in a short wire with its NET NAME; equal names are connected (also between blocks). A cross = intentionally unconnected pin.
Diode symbols point anode to cathode. Pin names are those of the library; items marked VERIFY in docs/ASSUMPTIONS.md are unverified. MODELED design: not built, not bench-tested.
PF233-AU1: AU1 audio board: descriptor link, MSPM0G3507 voice synth, TPA2005D1 speaker amp, TPA6132A2 headphone amp, 3-position output selector, BMI270 yaw gyro
1 Power: pack -> 5 V buck -> 3.3 V LDO
JPWR from PM2-B JAUP (switched, fused 0.5 A). UB TPS560430 (RFT / RFB set 5.0 V, LB 22 uH), UL TLV75533 3.3 V.
UL_NC
2 Controller
UM MSPM0G3507: DAC (PA15) for the voice, PWM (PA14) for the right channel, UART0 for the link; JSWD SWD pads, TPRST reset pad, RBSL keeps PA18 (BSL invoke) low.
UM_P1_NC
UM_P2_NC
UM_P12_NC
UM_P13_NC
UM_P14_NC
UM_P24_NC
UM_P25_NC
UM_P26_NC
UM_P27_NC
3 Descriptor link and output selector
JLINK from HB2-B JAU: half-duplex, TX through RTX 1 k, entry RLK 100 R with BAS16 clamps.
JSEL: 3-position selector to GND, pull-ups RS1-RS3 (AUDIO_ONLY / LED_ONLY / COMBINED).
4 Speaker amplifier
US TPA2005D1, gain 2 x 150 k / RI = 2 V/V, input caps CI1 / CI2, SHUTDOWN pulled low (RSD) until the MCU enables it; JSPK 8 ohm speaker.
US_NC
5 Headphone amplifier
UH TPA6132A2 DirectPath, 0 dB (G0 high, G1 low), single-ended inputs; left = DAC, right = RC-filtered PWM (RPW / CPW).
JHP: panel jack tip / ring / sleeve and plug-detect (RDT pull-up).
6 Yaw gyro (sweep direction, moved from CB1D)
UG BMI270 (alternate: ST LSM6DSO, same land) on I2C0, UM pins 4 / 5 (PA0 SDA / PA1 SCL); alternate address (SDO high); UG_VIO = VDD, VDDIO, CSB, SDO, pins 2 / 3,
fed from +3V3_AU by RGF 10 R with CG1 / CG2 100 nF; RGA / RGL 4k7 pull-ups. The yaw rate goes to the head in the link reply.
UG_INT1_NC
UG_INT2_NC
UG_OCSB_NC
UG_OSDO_NC

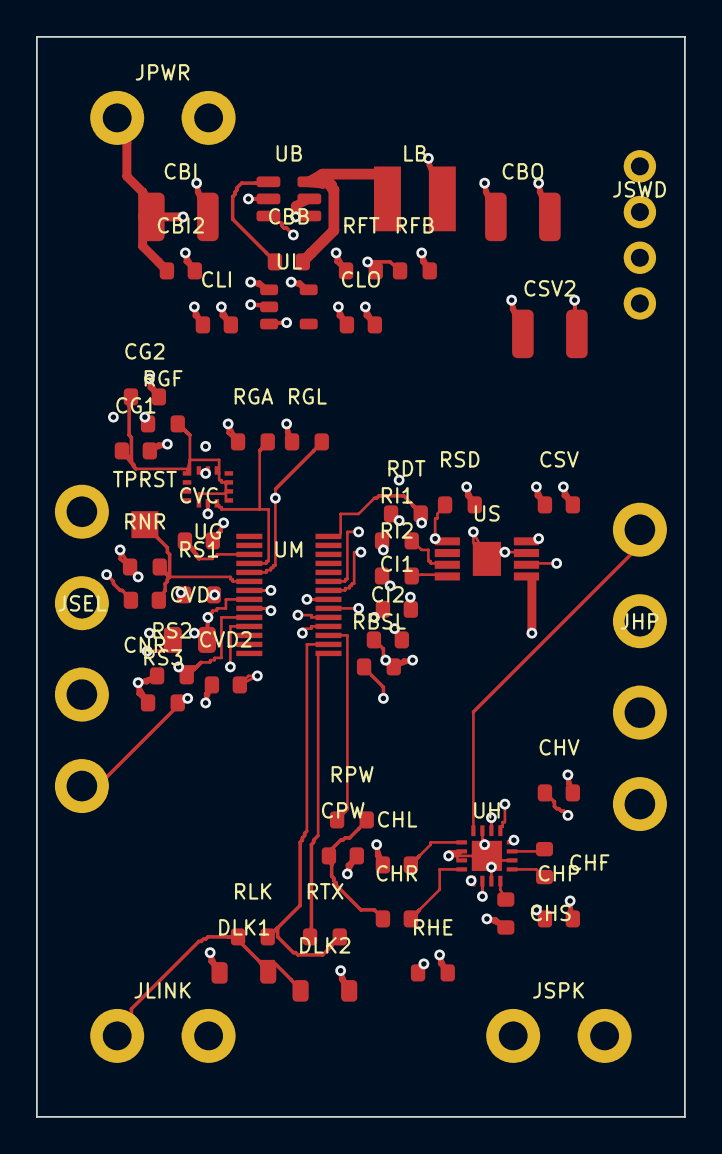
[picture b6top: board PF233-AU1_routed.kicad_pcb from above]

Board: 8 copper layers, 36.0 x 60.0 mm, 57 parts (0 on the bottom side), 41 nets.

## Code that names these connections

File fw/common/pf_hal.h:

/* Hardware abstraction for the PHI-FOLD 233 firmware. The target builds implement it on the Pico SDK (CB1D, RP2350: PIO for the gated ADC frames,
 * the SK9822 LED stream and the half-duplex link) and on the TI MSPM0 SDK / DriverLib (AU1: UART0, DAC12, TIMG12 PWM, GPIO, I2C0 for the gyro);
 * neither SDK is installed in this repository's container, so only the host stubs (fw/tests/hal_host.c) are built and run here. Every call that touches
 * the coil, the receive chain or the cord is issued by the scheduler only in the slot fw_timeline.py / output_modes.py allow. */
#pragma once
#include <stdint.h>
/* ---- CB1D (head) ---- */
void hal_tx_fire(uint32_t ton_ns);                                   /* TX1_IN high for ton, then off (PB1R) */
void hal_adc_gates(float gA[9], float gB[9]);                        /* gate means of QUAD-A / QUAD-B for the pulse just fired (PIO + AD7389-4) */
float hal_gyro_yaw_dps(void);                                        /* AU1 only: BMI270 / LSM6DSO z rate over I2C0 on PA0 / PA1 (address 0x69 / 0x6B: SDO high) */
int hal_trigger(void);                                               /* TRIG_IN high = pressed (boost) */
void hal_led_frame(const uint8_t *frame, int nbytes);                /* SK9822 frame on LED_IN / LED_CLK (PIO, 8 MHz) */
void hal_link_send(const uint8_t *b, int n);                         /* AUD_LINK, 1 Mbaud, then release the line */
int hal_link_reply(uint8_t *b, int n, uint32_t timeout_us);          /* bytes received from AU1 within the timeout */
void hal_wait_period_end(uint32_t period_ns);                        /* sleep to the next TX period boundary */
/* ---- AU1 (audio) ---- */
int au_link_recv(uint8_t *b, int n, uint32_t timeout_us);
void au_link_send(const uint8_t *b, int n);
int au_selector(void);                                               /* 0 AUDIO_ONLY, 1 LED_ONLY, 2 COMBINED (JSEL: SEL1..SEL3 active low) */
int au_headphones(void);                                             /* plug-detect */
void au_amp_enable(int speaker, int headphones);                     /* TPA2005D1 SHUTDOWN, TPA6132A2 EN */
void au_audio_out(const int16_t *left, const int16_t *right, int n); /* left -> DAC12 (PA15), right -> TIMG12 PWM (PA14) */

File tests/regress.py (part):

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else: skip("KiCad schematics")
d=rd("kit_v22/trigger_check.json")
if d: bad=[c["check"] for c in d["checks"] if c["result"]=="FAIL"]; chk("handle inputs: trigger chain, sensor type vs GPIO, TRIG levels and time constant, dial ladder, boost stress",not bad,f"{d['levels']}, fails {bad}")
else: skip("trigger check")
d=rd("kit_v22/head_crosscheck.json")
if d: chk("full head cross-check: 0 failures (layers, radial fits, 3D interference, LED, TX, RX, wiring)",d["fails"]==0,f"{len(d['checks'])} checks, warns {d['warns']}")
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    _bad=[_r[0] for _r in _csv.reader(open("releases/RX_r2/MANIFEST.csv")) if _r and len(_r)>2 and len(_r[2])==64 and (not os.path.exists(_r[0]) or hashlib.sha256(open(_r[0],"rb").read()).hexdigest()!=_r[2])]
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else: chk("release RX_r2 exists once RX_r1 is marked SUPERSEDED (no silent gap between revisions)",not os.path.exists("releases/RX_r1/SUPERSEDED.txt"),"RX_r2 not cut yet")
if os.path.isdir("releases/TX_r5"):                                   # 2026-10-28: TX_r5 = PB1R-v4 (CB7-CB9 pad angle) + CB1D-C1 (LED_CLK); TX_r4 stays as written and is marked SUPERSEDED
    import hashlib, csv as _csv, glob as _g
    _rm=open("releases/TX_r5/RELEASE.md").read(); _man=list(_csv.reader(open("releases/TX_r5/MANIFEST.csv")))
    _bad=[_r[0] for _r in _man if _r and len(_r)>2 and len(_r[2])==64 and (not os.path.exists(_r[0]) or hashlib.sha256(open(_r[0],"rb").read()).hexdigest()!=_r[2])]
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    _gd=[(_gg.layer_geometry(f)[0].symmetric_difference(_gg.layer_geometry_sequential(f)[0]).area) for f in _gf[:2]]
    chk("Gerber geometry: batched build equals the sequential build (hatched plane + fine-pitch signal layer)", len(_gd)==2 and max(_gd)<1e-6, f"sym-diff {[float(f'{d:.2g}') for d in _gd]} mm2 on {[os.path.basename(f) for f in _gf[:2]]}")
except Exception as e: chk("Gerber geometry batched vs sequential",False,f"{type(e).__name__}: {e}")
# rule 6 on the flyback nets (2026-10-28): every PB1R part on DRAIN1 / CLAMP1 that carries a voltage rating is >= 630 V (US3M replaced the 600 V ES3J; RCL1 = PR03 750 V)
try:
    _pc=[r for r in json.load(open("work/kit_v22/pb1r_check.json"))["checks"] if "630 V or better" in r["check"]][0]
    _low={k:v for k,v in _pc["value"].items() if v[1] is not None and v[1]<630}
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
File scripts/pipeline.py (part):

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    ("route-lb1", route("LB1"), ""),
    ("gerber-lb1", W + "python3 gerber_out.py LB1 hatch notch-1 && python3 gerber_edge_check.py kit_v22/gerber_edge_LB1.json kit_v22/GERBER_LB1_v2 PF233-LB1-v2", ""),
    ("route-cb1d", route("CB1D"), ""),
    ("gerber-cb1d", W + "python3 gerber_out.py CB1D hatch notch1 hv=COIL_A,COIL_B,DM1,DM2 && python3 gerber_hv_check.py CB1D kit_v22/GERBER_CB1D_v2 PF233-CB1D-v2 COIL_A,COIL_B,DM1,DM2 && python3 gerber_edge_check.py kit_v22/gerber_edge_CB1D.json kit_v22/GERBER_CB1D_v2 PF233-CB1D-v2", ""),
    ("route-pb1r", route("PB1R") + " && python3 viafarm.py PB1R kit_v20/route_PB1R.json", ""),
    ("drc-lb1", W + "python3 drc.py LB1 kit_v20/route_LB1.json -1", ""),
    ("drc-cb1d", W + "python3 drc.py CB1D kit_v20/route_CB1D.json 1 COIL_A,COIL_B,DM1,DM2", ""),
    ("drc-pb1r", W + "python3 drc.py PB1R kit_v20/route_PB1R.json 0 DRAIN1,CLAMP1", ""),
    ("kicad-lb1", "mkdir -p work/kit_v22/KICAD && " + W + "python3 kicad_inject.py LB1 kit_v20/route_LB1.json kit_v22/KICAD/PF233-LB1_routed.kicad_pcb -1", ""),
    ("kicad-cb1d", "mkdir -p work/kit_v22/KICAD && " + W + "python3 kicad_inject.py CB1D kit_v20/route_CB1D.json kit_v22/KICAD/PF233-CB1D_routed.kicad_pcb 1 six", ""),
    ("kicad-pb1r", "mkdir -p work/kit_v22/KICAD && " + W + "python3 rect_inject.py PB1R kit_v20/route_PB1R.json kit_v6/PB1R/PF233-PB1R.kicad_pcb kit_v22/KICAD/PF233-PB1R_routed.kicad_pcb", ""),
    ("gerber-pb1r", "python3 src/pcb/kicad_gerber.py work/kit_v22/KICAD/PF233-PB1R_routed.kicad_pcb PB1R work/kit_v22/GERBER_PB1R PF233-PB1R && "
                    + W + "python3 gerber_plane_check.py PB1R kit_v22/GERBER_PB1R PF233-PB1R DRAIN1,CLAMP1 In1:GND,In2:VBUS && python3 gerber_edge_check.py kit_v22/gerber_edge_PB1R.json kit_v22/GERBER_PB1R PF233-PB1R", "kicad"),
    ("route-pm2", route("PM2"), ""),
    ("drc-pm2", W + "python3 drc.py PM2 kit_v20/route_PM2.json 0", ""),
    ("kicad-pm2", "mkdir -p work/kit_v22/KICAD && " + W + "python3 rect_inject.py PM2 kit_v20/route_PM2.json kit_v6/PM2/PF233-PM2.kicad_pcb kit_v22/KICAD/PF233-PM2_routed.kicad_pcb", ""),
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
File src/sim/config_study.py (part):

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      changes=[]),
 "C1 light and balanced": dict(turns=1.0, hood="v4 one tile per spoke", upper="light (walls 2.0, dock 2.5)", pack="7S1P Molicel P30B (18650, as built)", N=100,
      changes=["hood carrier v4: one 55.5 mm tile per spoke (generator change, same carrier envelope)", "upper housings 2.0 mm walls, dock plate 2.5 mm (regenerated)",
               "PB1R bulk 35 V polymer Ta -> 50 V parts (29.4 V is 84 % of 35 V; about 80 % is the polymer-Ta guideline)", "firmware rules (constant-current ton, boost duty, BLANK policy, LED cap, TRIG boot rule)"]),
 "C2 early gate (12 turns per layer)": dict(turns=0.75, hood="v4 one tile per spoke", upper="light (walls 2.0, dock 2.5)", pack="7S1P Molicel P30B (18650, as built)", N=100,
      changes=["C1 changes", "six formers regenerated for 12 turns per layer (0.75 x), 26.7 A peak", "self-capacitance and damping chain re-derived for the new coil, then this study re-run",
               "PB1R: 26.7 A peak, 13.3 A per FET (44 % margin); shunt and OCP reference rescaled"]),
 "C3 endurance (P42A 21700 pack)": dict(turns=1.0, hood="v4 one tile per spoke", upper="light (walls 2.0, dock 2.5)", pack="7S1P Molicel P42A (21700)", N=100,
      changes=["C1 changes", "pack shell U7 regenerated for 7 x 21700 (21.7 x 70.2 mm) and the BMS bay; dock rails unchanged", "pack 0.16 kg heavier, behind the grip"]),
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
